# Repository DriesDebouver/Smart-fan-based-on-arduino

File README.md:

# Smart Fan

Smart 12V fan based on arduino controlled by PWM for a fridge cabinet with a LM335 temperature sensor.
Fan is silent under 25°C and kicks in above 25°C until 40°C when the maximum RPM is achieved.
RGB status LED is green under 25°C, blue between 25°C - 40°C and red above 40°C.

Exercise for the "Sensors & Interfacing" course in the Internet of Things education.

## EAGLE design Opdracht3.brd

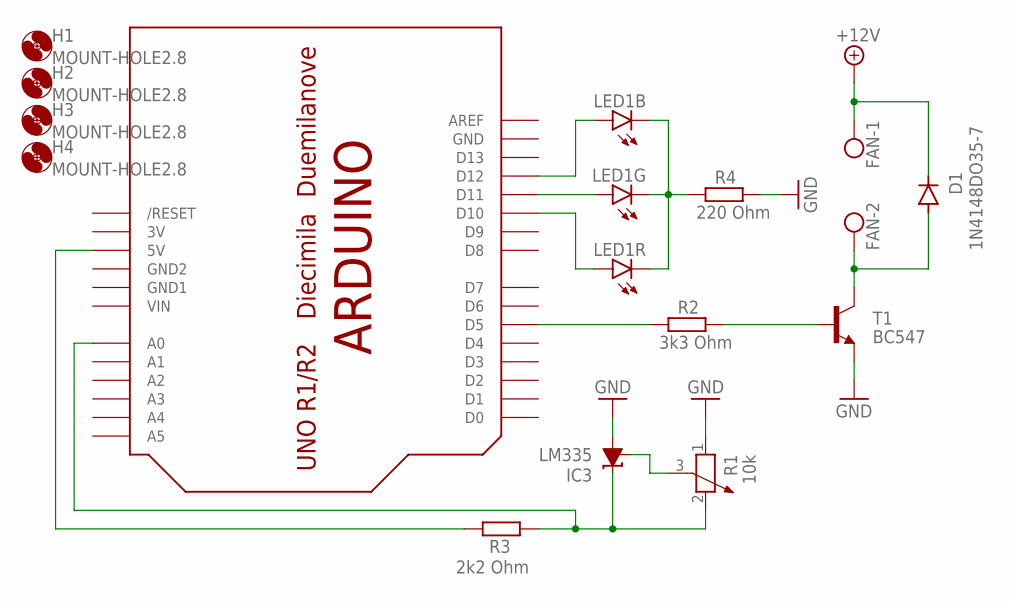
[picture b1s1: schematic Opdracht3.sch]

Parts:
D1: 1N4148DO35-7; DO35-7
FAN: W237-102
H1, H2, H3, H4: MOUNT-HOLE2.8; 2,8
IC3: LM335; LP_O-PBCY-W3
LED1: GM5WA94310A
R1: 10k; PT-10
R2: 3k3 Ohm; 0207/10
R3: 2k2 Ohm; 0207/10
R4: 220 Ohm; 0207/10
T1: BC547; TO92
U$1: ARDUINOUNO; ARDUINO

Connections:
3V: U$1.3V
+12V: D1.C, FAN.1
GND: IC3.3 (A), R1.1, R4.2, T1.1 (E), U$1.GND
GND1: U$1.GND1
GND2: U$1.GND2
unnamed: R3.2, U$1.5V
unnamed: IC3.2 (C), R1.2, R3.1, U$1.A0
unnamed: LED1.2 (A), U$1.D10
unnamed: LED1.3 (A), U$1.D11
unnamed: LED1.1 (A), U$1.D12
unnamed: IC3.1 (FB), R1.3
unnamed: R2.1, U$1.D5
unnamed: R2.2, T1.2 (B)
unnamed: D1.A, FAN.2, T1.3 (C)
unnamed: LED1.4 (C), LED1.5 (C), LED1.6 (C), R4.1
VIN: U$1.VIN

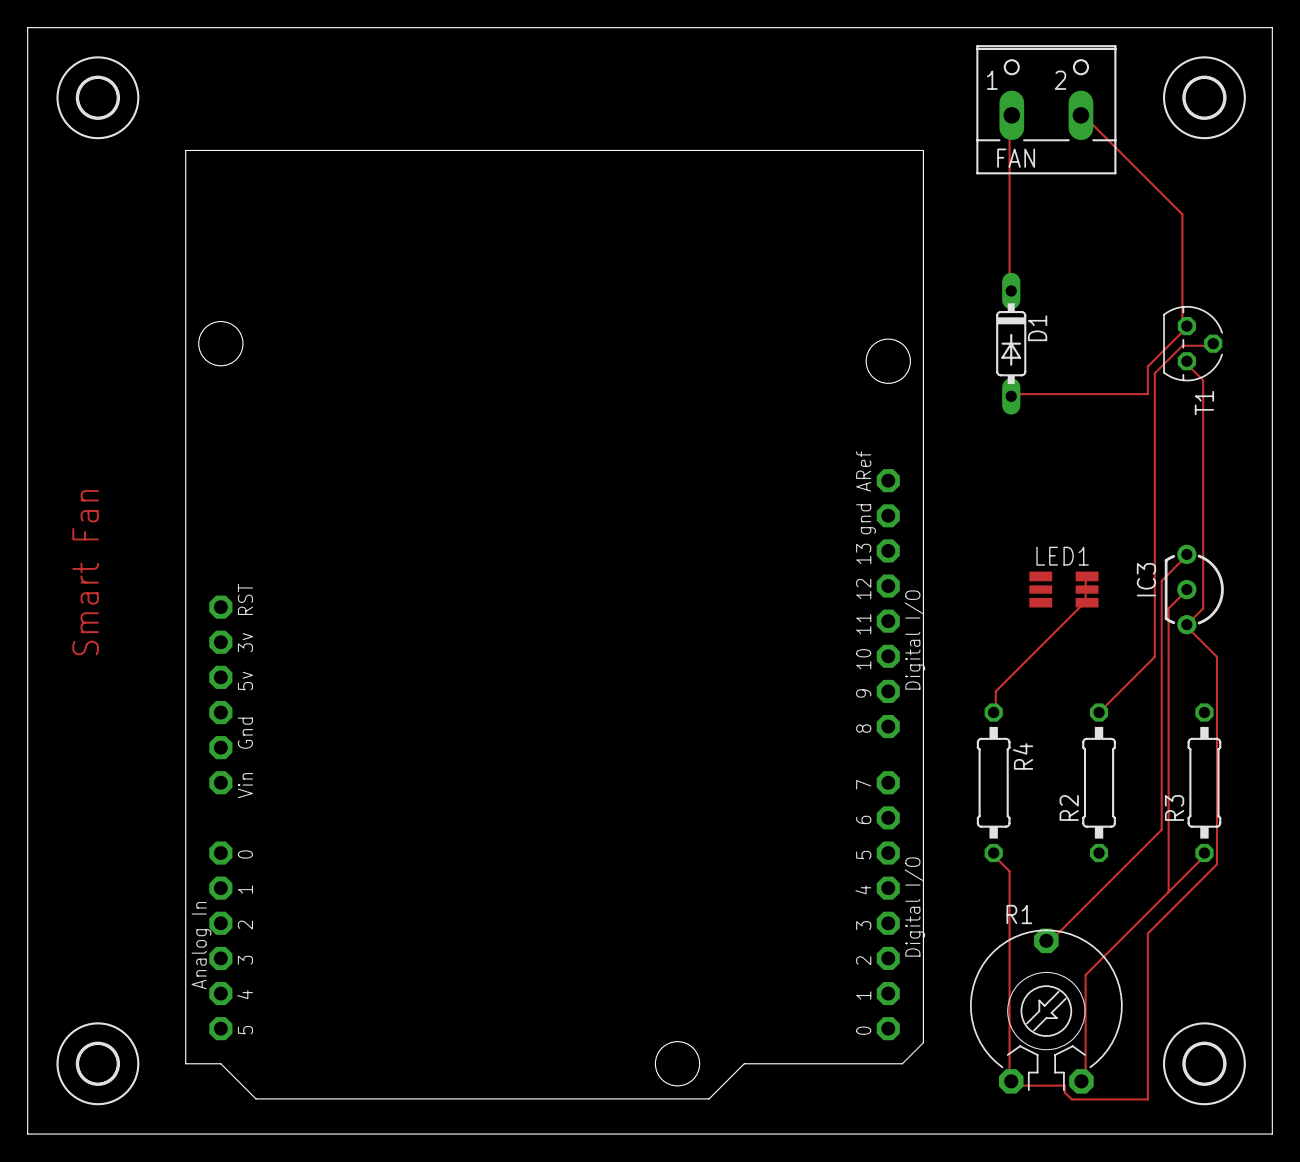
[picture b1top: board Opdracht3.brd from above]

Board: 2 copper layers, 90.0 x 80.0 mm, 14 parts (0 on the bottom side), 12 nets.

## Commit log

2020-02-23 Add files via upload
    Arduino Uno code
